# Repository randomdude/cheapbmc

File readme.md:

= About = 

This is a very simple tool to control a PC's power state. It offers functions to 'press' the power button (controlled via a relay), the 'reset' button, and to observe the current power state of the PC.

It connects to the PC's ATX power-supply header, and uses an ESP8266 to expose a web interface via SSL. The web interface uses mutual SSL (ie, the client authenticates with a certificate and the server authenticates with a certificate).

= Building =

Refer to the Jenkinsfile, or:

```
git clone https://github.com/Microsoft/vcpkg.git
cd vcpkg
bootstrap-vcpkg.bat
vcpkg integrate install
vcpkg install curl[tool] curl[openssl]
```

You'll need to generate keys first - cd to keys/ and run `generate.sh`.

= Use = 

There's no real commandline tool yet (TODO!) but you can test with cURL.

```
# curl --cert access.crt --key access.key --cacert ca.crt https://192.168.90.23 
<html><head></head><a href="doPower">Power button control</a></br><a href="doReset">Reset button control</a></br><a href="getTargetStatus">Get target power LED state</a></br></html>
# curl --cert access.crt --key access.key --cacert ca.crt https://192.168.90.23/getTargetStatus 
OFF
aliz@nuc:/foo# curl -X POST --cert access.crt --key access.key --cacert ca.crt https://192.168.90.23/doPower?thingToDo=short
```

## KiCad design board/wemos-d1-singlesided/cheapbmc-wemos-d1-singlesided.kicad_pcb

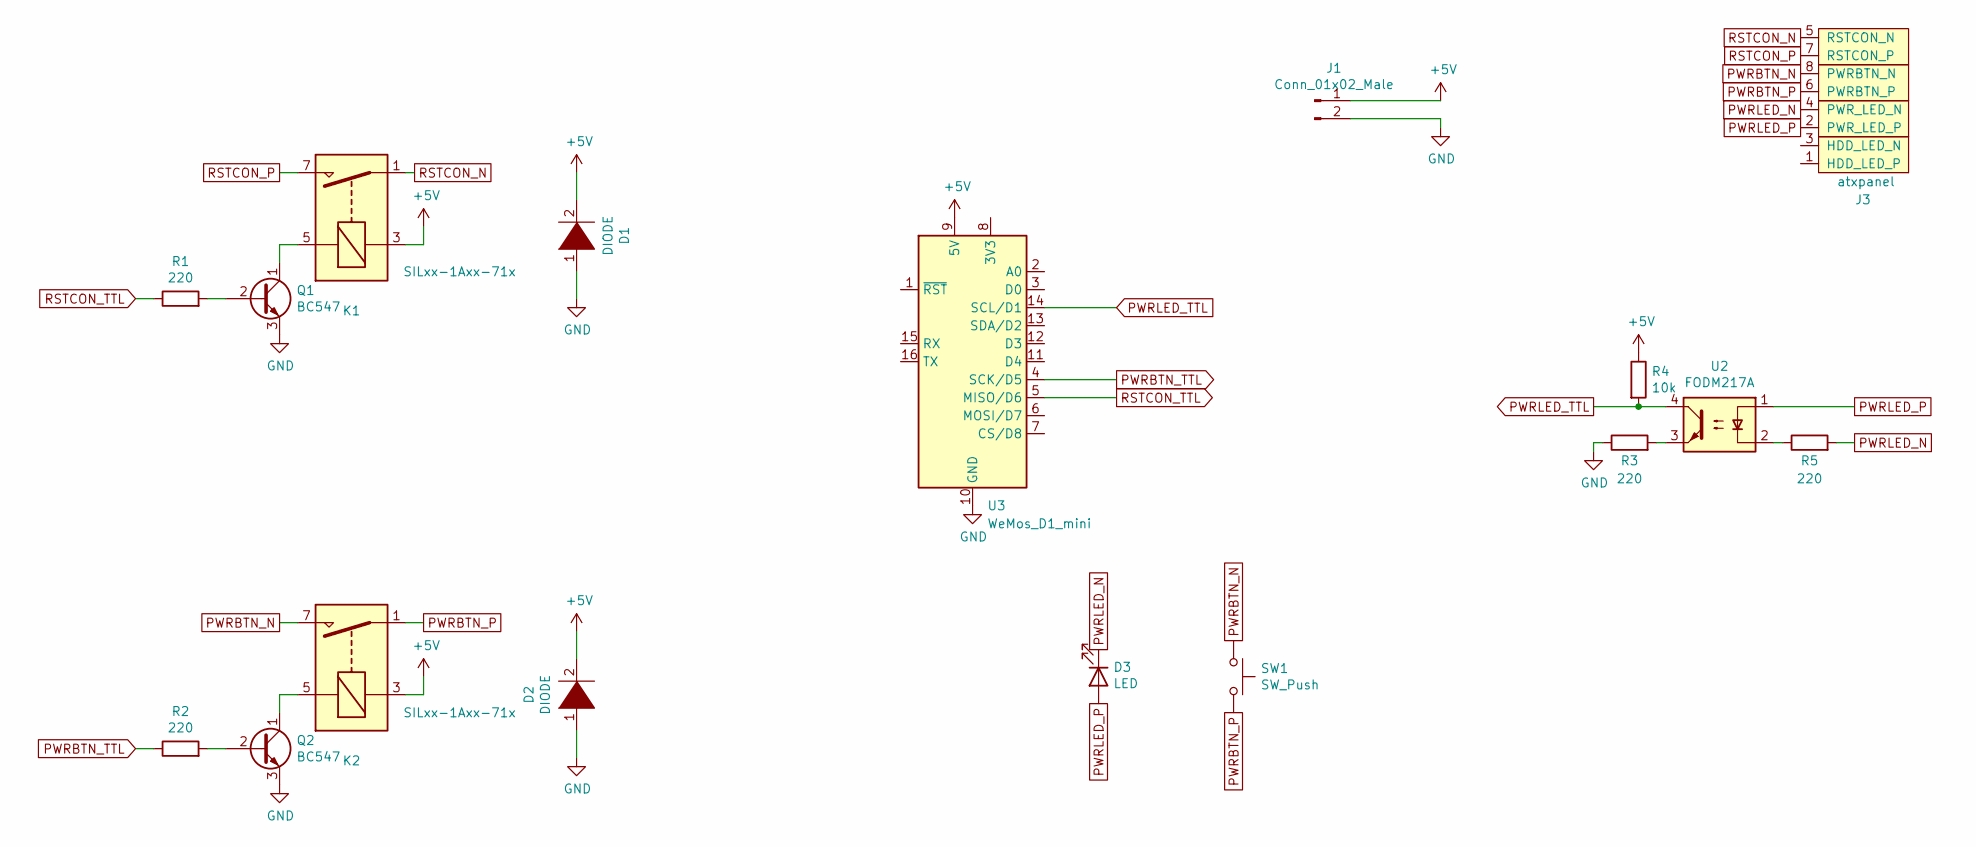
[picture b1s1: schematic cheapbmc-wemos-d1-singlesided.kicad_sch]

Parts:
D1, D2: DIODE; D_A-405_P7.62mm_Horizontal
D3: LED; LED_D3.0mm
J1: Conn_01x02_Male; PinHeader_1x02_P2.54mm_Vertical
J3: atxpanel; atx-panel-horz-inverted
K1, K2: SILxx-1Axx-71x; Relay_SPST_StandexMeder_SIL_Form1A
Q1, Q2: BC547; TO-92_Inline_Wide
R1, R2, R3, R5: 220; R_Axial_DIN0204_L3.6mm_D1.6mm_P7.62mm_Horizontal
R4: 10k; R_Axial_DIN0204_L3.6mm_D1.6mm_P7.62mm_Horizontal
SW1: SW_Push; SW_Tactile_SKHH_Angled
U2: FODM217A; DIP-4_W7.62mm
U3: WeMos_D1_mini; WEMOS_D1_mini_light

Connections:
+5V: D1.2 (A), D2.2 (A), J1.1, K1.3, K2.3, R4.1, U3.9 (5V)
GND: D1.1 (K), D2.1 (K), J1.2, Q1.3 (E), Q2.3 (E), R3.1, U3.10 (GND)
unnamed: K1.5, Q1.1 (C)
unnamed: K2.5, Q2.1 (C)
unnamed: Q1.2 (B), R1.2
unnamed: Q2.2 (B), R2.2
unnamed: R3.2, U2.3
unnamed: R5.1, U2.2
PWRBTN_N: J3.8 (PWRBTN_N), K2.7, SW1.1
PWRBTN_P: J3.6 (PWRBTN_P), K2.1, SW1.2
PWRBTN_TTL: R2.1, U3.4 (SCK/D5)
PWRLED_N: D3.1 (K), J3.4 (PWR_LED_N), R5.2
PWRLED_P: D3.2 (A), J3.2 (PWR_LED_P), U2.1
PWRLED_TTL: R4.2, U2.4, U3.14 (SCL/D1)
RSTCON_N: J3.5 (RSTCON_N), K1.1
RSTCON_P: J3.7 (RSTCON_P), K1.7
RSTCON_TTL: R1.1, U3.5 (MISO/D6)

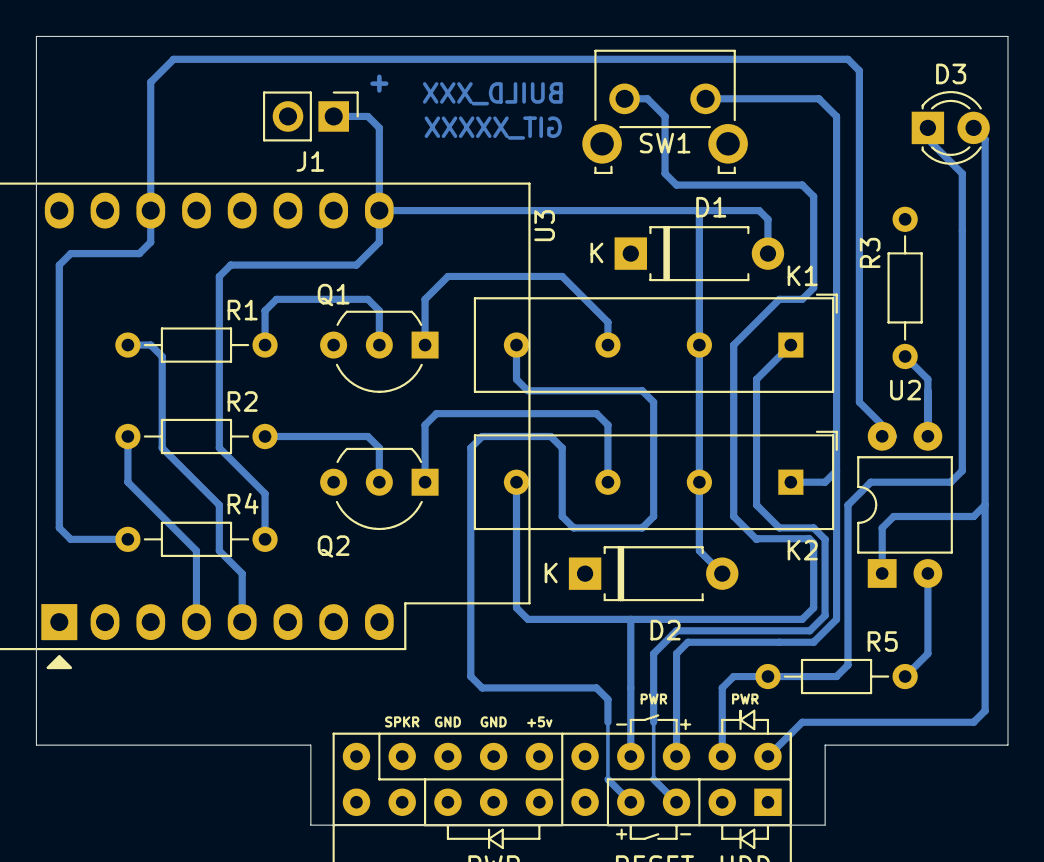
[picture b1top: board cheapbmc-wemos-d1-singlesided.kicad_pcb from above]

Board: 2 copper layers, 54.0 x 43.8 mm, 17 parts (0 on the bottom side), 17 nets.

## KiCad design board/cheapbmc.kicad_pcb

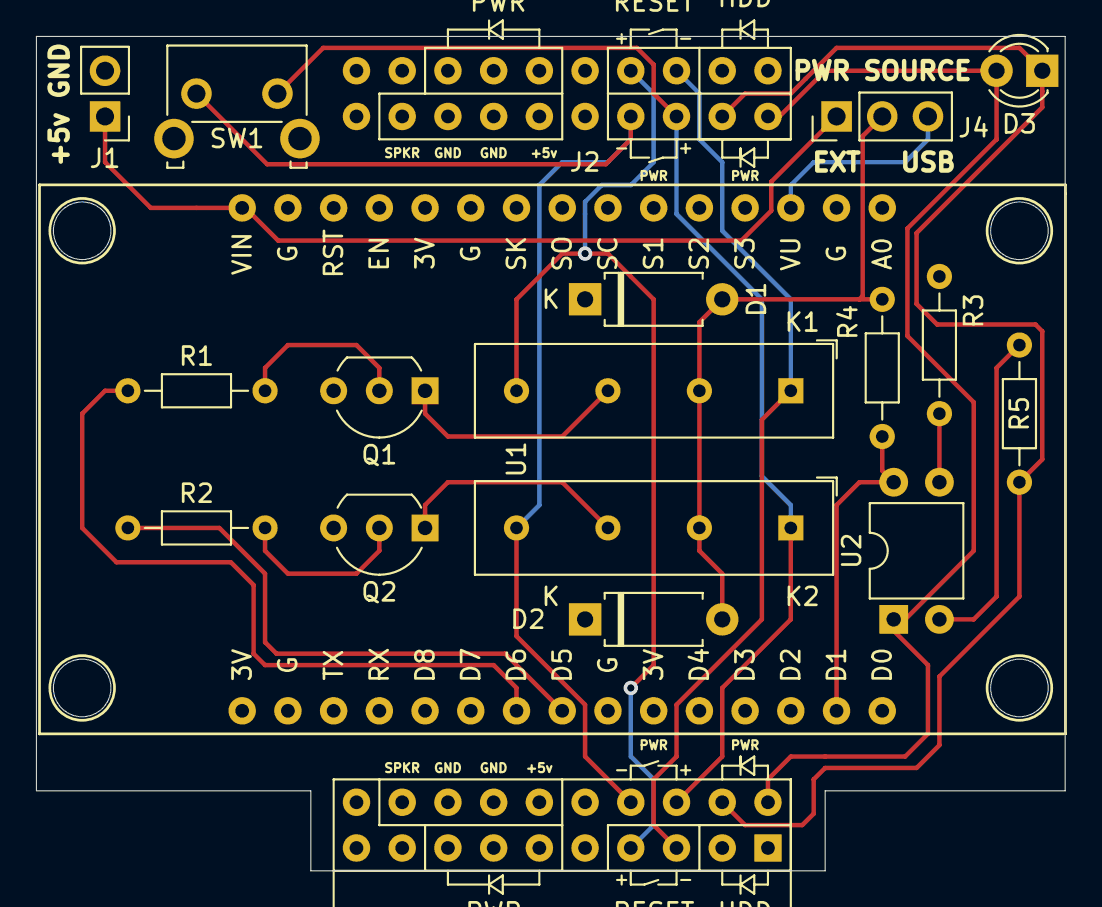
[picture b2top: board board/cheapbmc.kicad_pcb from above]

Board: 2 copper layers, 57.2 x 46.4 mm, 23 parts (0 on the bottom side), 19 nets.

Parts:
D1, D2: DIODE; D_A-405_P7.62mm_Horizontal
D3: LED; LED_D3.0mm
H1, H2, H3, H4: MountingHole; MountingHole_3.2mm_M3
J1: Conn_01x02_Male; PinHeader_1x02_P2.54mm_Vertical
J2: atxpanel; atx-panel
J3: atxpanel; atx-panel-horz-inverted
J4: Conn_01x03_Male; PinHeader_1x03_P2.54mm_Vertical
K1, K2: SILxx-1Axx-71x; Relay_SPST_StandexMeder_SIL_Form1A
Q1, Q2: BC547; TO-92_Inline_Wide
R1, R2, R3, R5: 220; R_Axial_DIN0204_L3.6mm_D1.6mm_P7.62mm_Horizontal
R4: 10k; R_Axial_DIN0204_L3.6mm_D1.6mm_P7.62mm_Horizontal
SW1: SW_Push; SW_Tactile_SKHH_Angled
U1: NodeMCU1.0(ESP-12E); NodeMCU-LoLinV3
U2: FODM217A; DIP-4_W7.62mm

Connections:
+5V: D1.2 (A), D2.2 (A), J4.2, K1.3, K2.3, R4.1
GND: D1.1 (K), D2.1 (K), J1.2, Q1.3 (E), Q2.3 (E), R3.1, U1.10 (GND)
unnamed: J1.1, J4.1, U1.15 (VIN)
unnamed: J4.3, U1.3 (RSV)
unnamed: K1.5, Q1.1 (C)
unnamed: K2.5, Q2.1 (C)
unnamed: Q1.2 (B), R1.2
unnamed: Q2.2 (B), R2.2
unnamed: R3.2, U2.3
unnamed: R5.1, U2.2
PWRBTN_N: J2.8 (PWRBTN_N), J3.8 (PWRBTN_N), K2.7, SW1.1
PWRBTN_P: J2.6 (PWRBTN_P), J3.6 (PWRBTN_P), K2.1, SW1.2
PWRBTN_TTL: R2.1, U1.23 (D5(GPIO14))
PWRLED_N: D3.1 (K), J2.4 (PWR_LED_N), J3.4 (PWR_LED_N), R5.2
PWRLED_P: D3.2 (A), J2.2 (PWR_LED_P), J3.2 (PWR_LED_P), U2.1
PWRLED_TTL: R4.2, U1.29 (D1(GPIO5)), U2.4
RSTCON_N: J2.5 (RSTCON_N), J3.5 (RSTCON_N), K1.1
RSTCON_P: J2.7 (RSTCON_P), J3.7 (RSTCON_P), K1.7
RSTCON_TTL: R1.1, U1.22 (D6(GPIO12))

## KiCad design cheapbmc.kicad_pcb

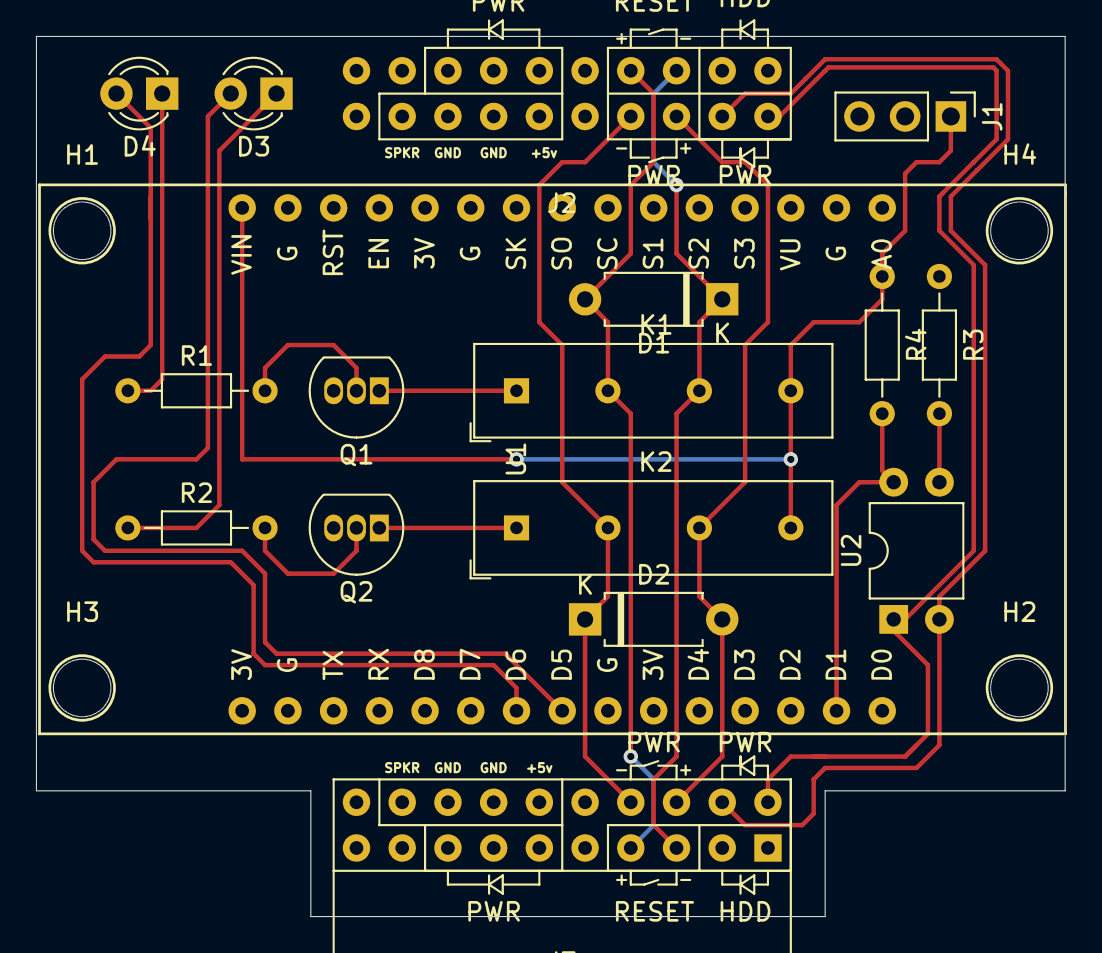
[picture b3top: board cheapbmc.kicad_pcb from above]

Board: 2 copper layers, 57.2 x 48.9 mm, 21 parts (0 on the bottom side), 18 nets.

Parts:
D1, D2: DIODE; D_A-405_P7.62mm_Horizontal
D3, D4: LED; LED_D3.0mm
H1, H2, H3, H4: MountingHole; MountingHole_3.2mm_M3
J1: Conn_01x03_Male; PinHeader_1x03_P2.54mm_Vertical
J2: atxpanel; atx-panel
J3: atxpanel; atx-panel-horz-inverted
K1, K2: SILxx-1Axx-71x; Relay_SPST_StandexMeder_SIL_Form1A
Q1, Q2: BC547; TO-92_Inline
R1, R2, R3: 220; R_Axial_DIN0204_L3.6mm_D1.6mm_P7.62mm_Horizontal
R4: 10k; R_Axial_DIN0204_L3.6mm_D1.6mm_P7.62mm_Horizontal
U1: NodeMCU1.0(ESP-12E); NodeMCU-LoLinV3
U2: FODM217A; DIP-4_W7.62mm

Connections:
+5V: J1.1, K1.7, K2.7, R4.1, U1.15
GND: J1.3, Q1.3, Q2.3, R3.1, U1.10
unnamed: D3.2, U1.23
unnamed: D4.2, U1.22
unnamed: K1.1, Q1.1
unnamed: K2.1, Q2.1
unnamed: Q1.2, R1.2
unnamed: Q2.2, R2.2
unnamed: R3.2, U2.3
PWRBTN_N: D2.1, J2.8, J3.8, K2.3
PWRBTN_P: D2.2, J2.6, J3.6, K2.5
PWRBTN_TTL: D3.1, R2.1
PWRLED_N: J2.4, J3.4, U2.2
PWRLED_P: J2.2, J3.2, U2.1
PWRLED_TTL: R4.2, U1.29, U2.4
RSTCON_N: D1.1, J2.5, J3.5, K1.5
RSTCON_P: D1.2, J2.7, J3.7, K1.3
RSTCON_TTL: D4.1, R1.1

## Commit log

2021-04-21 Add some mounting holes
2021-04-21 move R4 out of H4's courtyard
2021-04-21 Rotate around input panel connector
2021-04-21 add jenkinsfile
2021-04-21 Improve front-panel footprint, add git/build silk
2021-04-21 Add docs
2021-04-21 Add uC code to repo
2021-04-21 Move board into /board directory
2021-04-21 Correct esp8266 submodule
2021-04-21 Correct path to kicad project
2021-04-21 Build uC code on jenkins
2021-04-21 fix slash direction, grr
2021-04-22 rename .ino to code.ino
2021-04-22 Try building using vmicro
2021-04-26 Build vsmicro project correctly
2021-05-14 Enlarge transistor footprints, correct relay footprint, add power selector switch, power LED/buttons
2021-05-14 run file recovery
2021-05-16 Move connector away from mounting hole
2021-05-16 adjust gnd/5v silk
2021-05-16 remove text from mounting holes
2021-07-10 Get client auth working
2021-08-12 add lib to use, tests, move stuff around
2021-08-12 gitignore some stuff
2021-08-12 Add libcurl via vcpkg
2021-08-19 get submodules when cloning
2021-08-19 typo
2021-08-19 noot
2021-08-27 Package into nuget package; support power button presses from .net
2021-08-27 Add example settings files
2021-08-27 initsettings.ps1 goes in repo root
2021-08-27 Correct vcpkg invokation
2021-08-27 correct path
2021-09-13 Fix settings name, correct vcproj filename in jenkinsfile
2021-09-13 correct path to built object
2021-09-13 rename template files
2021-09-15 mess with nuget, mostly
2021-09-15 update gitignore
2021-10-06 Remove libcurl, change nuget to provide a single managed package
2021-10-06 Remove leftovers from libcurl nuget package
2021-10-06 attempt to stop jenkins trying to build uC code via VS and not vsmicro
2021-10-06 remove libcurl.dll and LibCurlShim.dll stuff
2021-10-06 Correct deployment of native dlls
2021-10-06 openssl build
2021-10-06 check board in parallel with build
2021-10-06 correct malformed .targets file in nuget pkg
2021-10-06 add missing close-bracket
2021-10-06 correct path to built objects
2021-10-07 merge
2021-10-07 Jump through hoops, make things work under AnyCPU
2021-10-07 correct msbuild target paths
2021-10-07 Correct build deps
2022-01-04 Create vcpkg directory if not existing already
2022-01-04 correct location of vcpkg directory
2022-01-04 correct location of vcpkg directory (again)
2022-01-24 don't import CSharp.targets if it is already imported
2022-02-03 board: Add current-limiting resistor on power status optoisolator
2022-04-16 Move to kicad 6
2022-04-16 Add kicad6 project files
2022-07-24 fix DRC, tidy up a bit
2022-07-24 Update libcrypto and libssl filenames, ugh
2022-12-03 make readme/docs a bit better
2022-12-06 move HTML into PROGMEM
2022-12-06 use basic ssl ciphers only
2022-12-16 add wemos-d1 board
2022-12-17 resove
2022-12-19 produce lpkf cam files
2023-01-05 keys: bump to 10-year expiry, add cert for 90.23
2023-01-05 Fix operation when power button is PWM'ed
2023-01-09 wemos: avoid 0.8mm drill because of broken 0.8mm drill bit
2023-07-04 Add 3.5-inch-disk-sized enclosure
2023-07-04 rotate some parts
2023-07-04 ensure we check out main project before trying to build enclosure
2023-07-04 tweak readme
